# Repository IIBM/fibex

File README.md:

# FIBEX
**FI**UBA **B**rain **EX**plorer

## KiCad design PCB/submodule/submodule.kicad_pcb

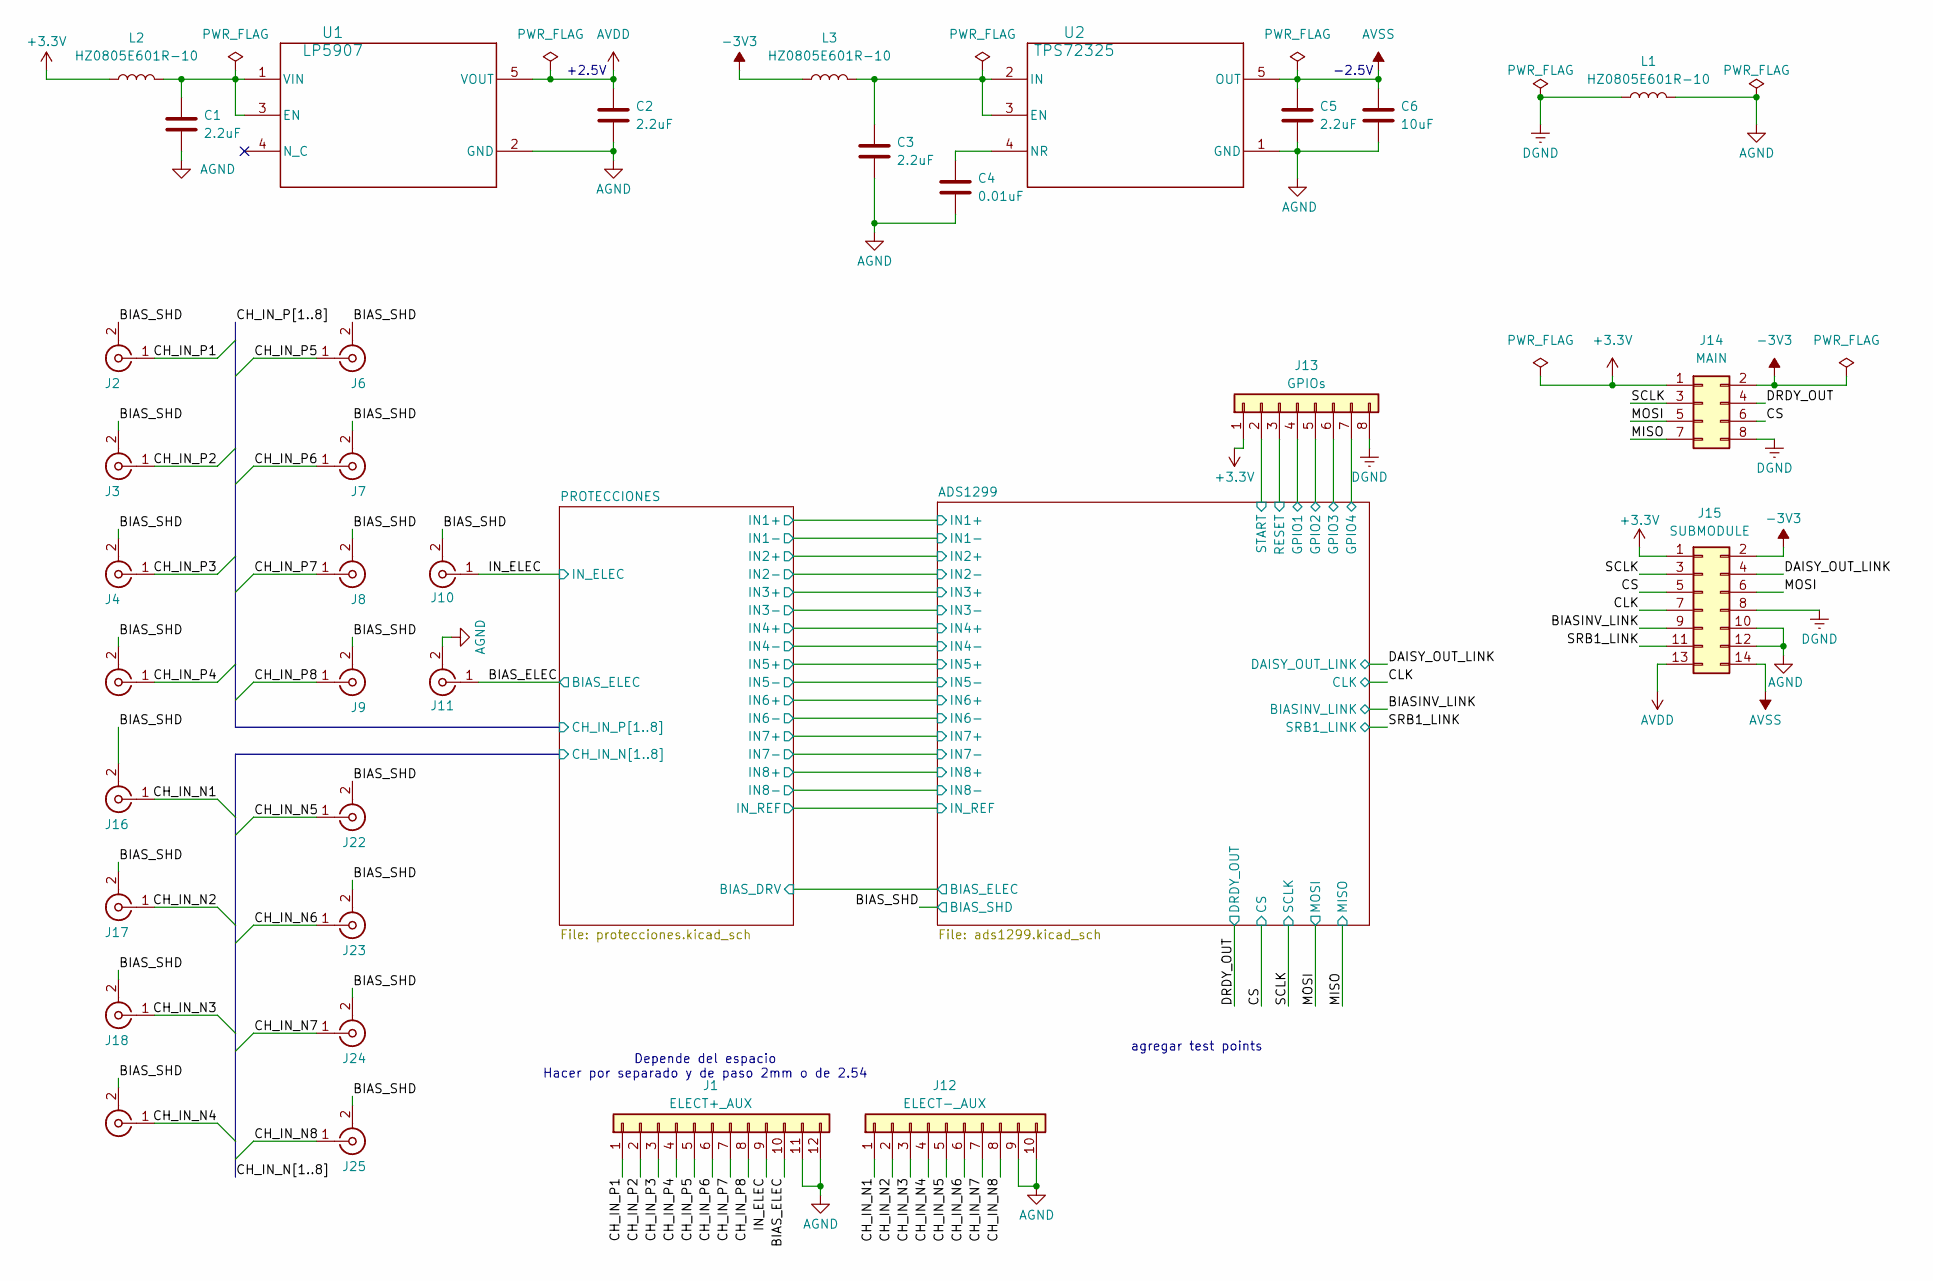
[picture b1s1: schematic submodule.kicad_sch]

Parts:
C1, C2, C3, C5: 2.2uF; C_0603_1608Metric
C4: 0.01uF; C_0603_1608Metric
C6: 10uF; C_0805_2012Metric
J1: ELECT+_AUX; PinHeader_1x12_P1.27mm_Vertical
J2, J3, J4, J5, J6, J7, J8, J9, J10, J11, J16, J17, J18, J21, J22, J23, J24, J25: Conn_Coaxial; U.FL_Molex_MCRF_73412-0110_Vertical
J12: ELECT-_AUX; PinHeader_1x10_P1.27mm_Vertical
J13: GPIOs; PinHeader_1x08_P1.27mm_Vertical
J14: MAIN; IDC-Header_2x04_P2.54mm_Vertical
J15: SUBMODULE; PinHeader_2x07_P1.27mm_Vertical
L1, L2, L3: HZ0805E601R-10; L_0805_2012Metric
U1: LP5907; SOT-23-5_TI_DBV0005A_N
U2: TPS72325; SOT-23-5_TI_DBV0005A_N

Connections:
+3.3V: J13.1, J14.1, J15.1, L2.1; also elsewhere on the board
-3V3: J14.2, J15.2, L3.1
/ADS1299/GPIO1: J13.4; also elsewhere on the board
/ADS1299/GPIO2: J13.5; also elsewhere on the board
/ADS1299/GPIO3: J13.6; also elsewhere on the board
/ADS1299/GPIO4: J13.7; also elsewhere on the board
/ADS1299/RESET: J13.3; also elsewhere on the board
/ADS1299/START: J13.2; also elsewhere on the board
/BIASINV_LINK: J15.9; also elsewhere on the board
/BIAS_ELEC: J1.10, J11.1 (In); also elsewhere on the board
/BIAS_SHD: J2.2 (Ext), J3.2 (Ext), J4.2 (Ext), J5.2 (Ext), J6.2 (Ext), J7.2 (Ext), J8.2 (Ext), J9.2 (Ext), J10.2 (Ext), J16.2 (Ext), J17.2 (Ext), J18.2 (Ext), J21.2 (Ext), J22.2 (Ext), J23.2 (Ext), J24.2 (Ext), J25.2 (Ext); also elsewhere on the board
/CH_IN_N1: J12.1, J16.1 (In); also elsewhere on the board
/CH_IN_N2: J12.2, J17.1 (In); also elsewhere on the board
/CH_IN_N3: J12.3, J18.1 (In); also elsewhere on the board
/CH_IN_N4: J12.4, J21.1 (In); also elsewhere on the board
/CH_IN_N5: J12.5, J22.1 (In); also elsewhere on the board
/CH_IN_N6: J12.6, J23.1 (In); also elsewhere on the board
/CH_IN_N7: J12.7, J24.1 (In); also elsewhere on the board
/CH_IN_N8: J12.8, J25.1 (In); also elsewhere on the board
/CH_IN_P1: J1.1, J2.1 (In); also elsewhere on the board
/CH_IN_P2: J1.2, J3.1 (In); also elsewhere on the board
/CH_IN_P3: J1.3, J4.1 (In); also elsewhere on the board
/CH_IN_P4: J1.4, J5.1 (In); also elsewhere on the board
/CH_IN_P5: J1.5, J6.1 (In); also elsewhere on the board
/CH_IN_P6: J1.6, J7.1 (In); also elsewhere on the board
/CH_IN_P7: J1.7, J8.1 (In); also elsewhere on the board
/CH_IN_P8: J1.8, J9.1 (In); also elsewhere on the board
/CLK: J15.7; also elsewhere on the board
/CS: J14.6, J15.5; also elsewhere on the board
/DAISY_OUT_LINK: J15.4; also elsewhere on the board
/DRDY_OUT: J14.4; also elsewhere on the board
/IN_ELEC: J1.9, J10.1 (In); also elsewhere on the board
/MISO: J14.7; also elsewhere on the board
/MOSI: J14.5, J15.6; also elsewhere on the board
/SCLK: J14.3, J15.3; also elsewhere on the board
/SRB1_LINK: J15.11; also elsewhere on the board
AGND: C1.2, C2.2, C3.2, C4.2, C5.2, C6.2, J1.11, J1.12, J11.2 (Ext), J12.9, J12.10, J15.10, J15.12, L1.2, U1.2 (GND), U2.1 (GND); also elsewhere on the board
AVDD: C2.1, J15.13, U1.5 (VOUT); also elsewhere on the board
AVSS: C5.1, C6.1, J15.14, U2.5 (OUT); also elsewhere on the board
DGND: J13.8, J14.8, J15.8, L1.1; also elsewhere on the board
unnamed: C1.1, L2.2, U1.1 (VIN), U1.3 (EN)
unnamed: C3.1, L3.2, U2.2 (IN), U2.3 (EN)
unnamed: C4.1, U2.4 (NR)

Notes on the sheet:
Depende del espacio Hacer por separado y de paso 2mm o de 2.54
+2.5V
agregar test points
-2.5V

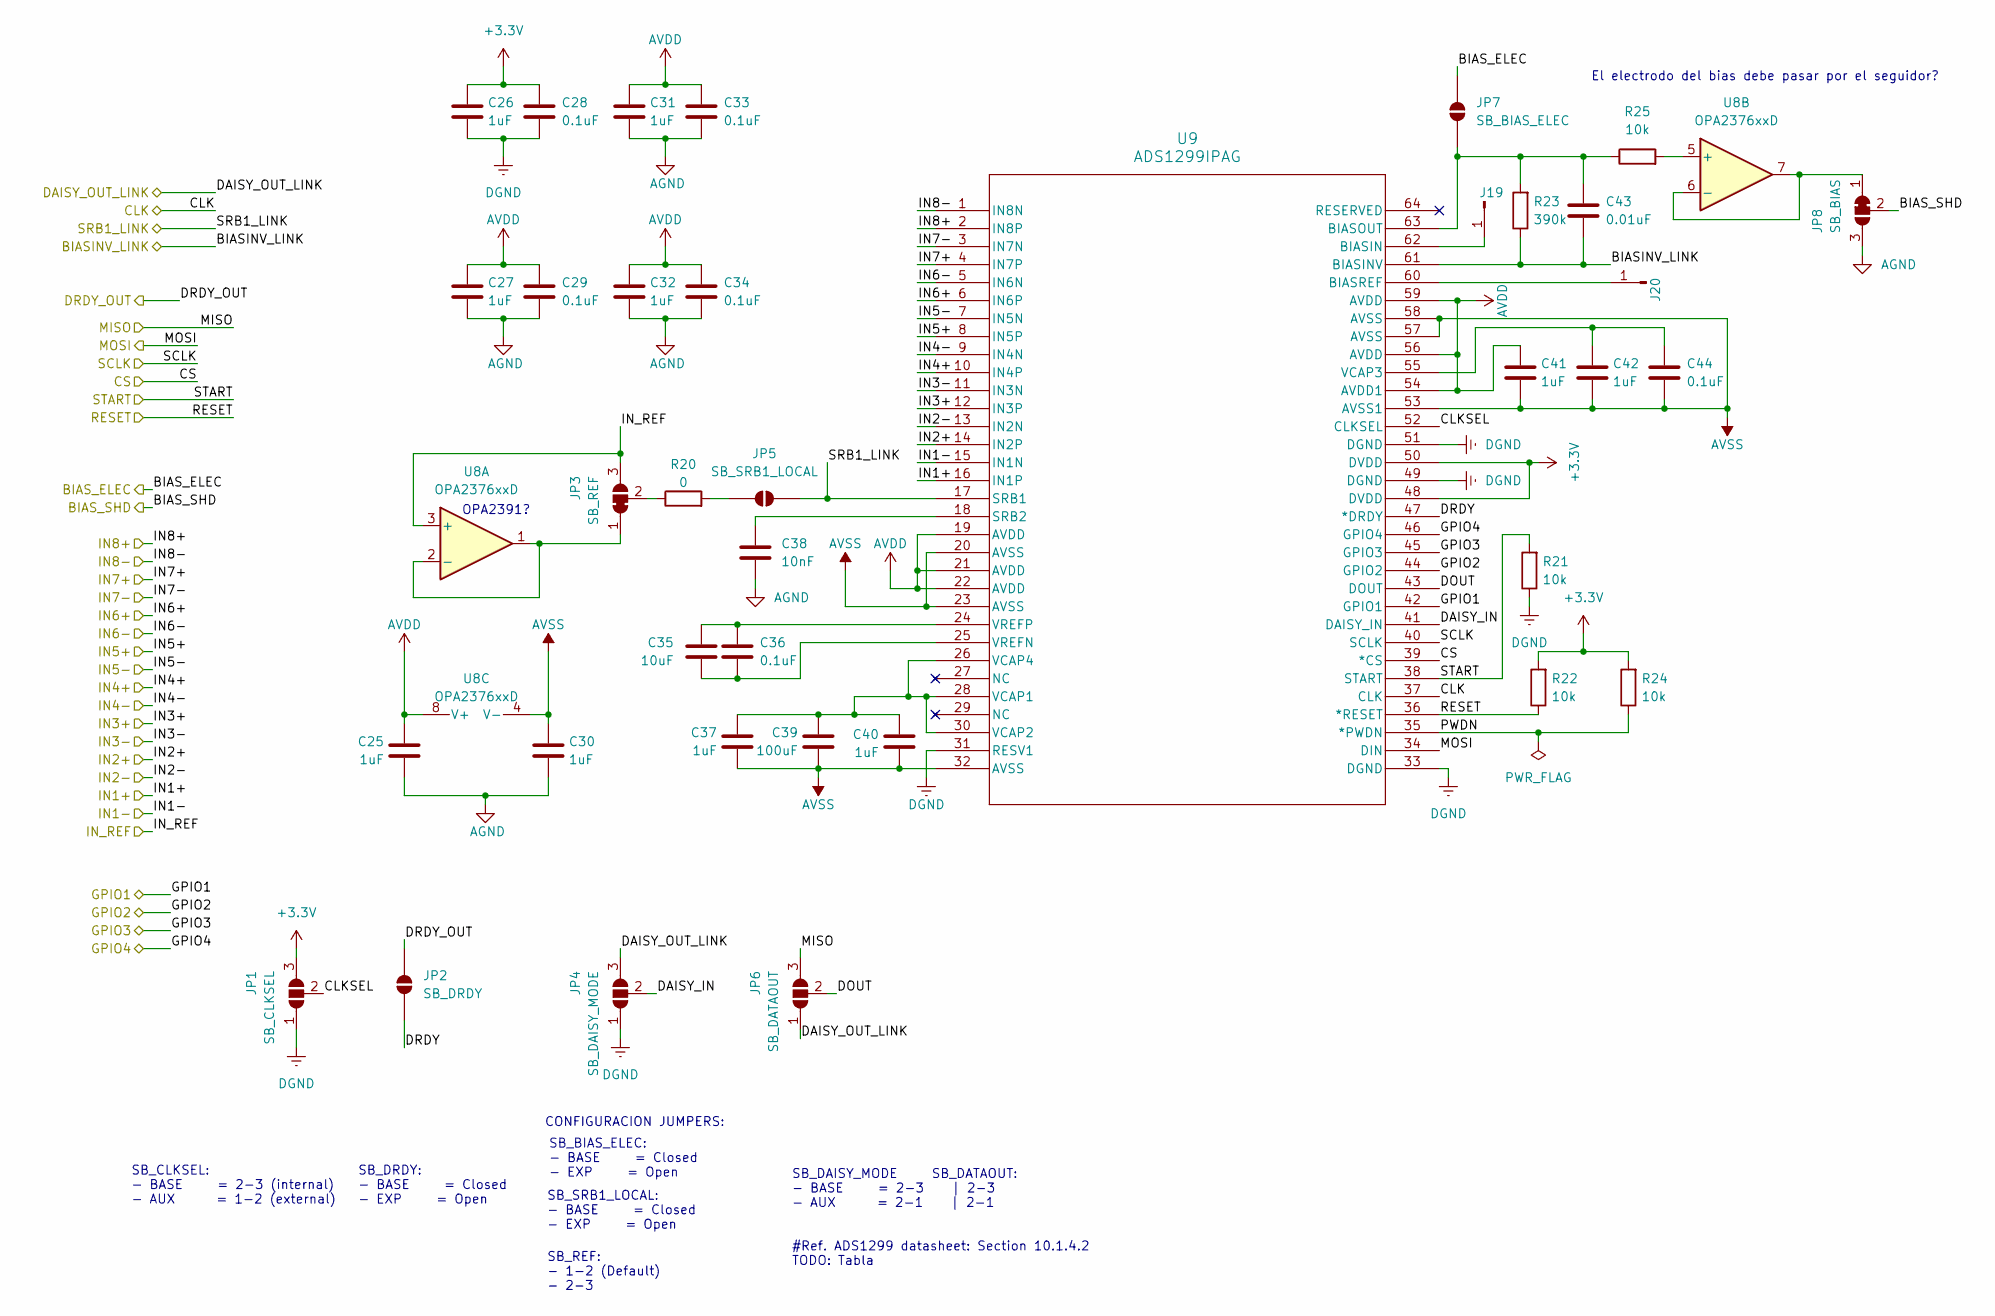
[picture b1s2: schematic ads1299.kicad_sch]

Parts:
C25, C26, C27, C30, C31, C32, C37, C40, C41, C42: 1uF; C_0603_1608Metric
C28, C29, C33, C34, C36, C44: 0.1uF; C_0603_1608Metric
C35: 10uF; C_0805_2012Metric
C38: 10nF; C_0603_1608Metric
C39: 100uF; C_1210_3225Metric
C43: 0.01uF; C_0603_1608Metric
J19, J20: Conn_01x01_Pin; SolderWirePad_1x01_SMD_1x2mm
JP1: SB_CLKSEL; SolderJumper-3_P2.0mm_Open_TrianglePad1.0x1.5mm_NumberLabels
JP2: SB_DRDY; SolderJumper-2_P1.3mm_Open_TrianglePad1.0x1.5mm
JP3: SB_REF; SolderJumper-3_P1.3mm_Bridged12_Pad1.0x1.5mm_NumberLabels
JP4: SB_DAISY_MODE; SolderJumper-3_P2.0mm_Open_TrianglePad1.0x1.5mm_NumberLabels
JP5: SB_SRB1_LOCAL; SolderJumper-2_P1.3mm_Open_TrianglePad1.0x1.5mm
JP6: SB_DATAOUT; SolderJumper-3_P2.0mm_Open_TrianglePad1.0x1.5mm_NumberLabels
JP7: SB_BIAS_ELEC; SolderJumper-2_P1.3mm_Open_TrianglePad1.0x1.5mm
JP8: SB_BIAS; SolderJumper-3_P1.3mm_Bridged12_Pad1.0x1.5mm_NumberLabels
R20: 0; R_0603_1608Metric
R21, R22, R24, R25: 10k; R_0603_1608Metric
R23: 390k; R_0603_1608Metric
U8: OPA2376xxD; SOIC-8_5.3x6.2mm_P1.27mm
U9: ADS1299IPAG; PAG64_TEX

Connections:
+3.3V: C26.1, C28.1, JP1.3 (B), R22.2, R24.2, U9.48 (DVDD), U9.50 (DVDD); also elsewhere on the board
/ADS1299/BIAS_ELEC: JP7.2 (B); also elsewhere on the board
/ADS1299/CLKSEL: JP1.2 (C), U9.52 (CLKSEL)
/ADS1299/DAISY_IN: JP4.2 (C), U9.41 (DAISY_IN)
/ADS1299/DOUT: JP6.2 (C), U9.43 (DOUT)
/ADS1299/DRDY: JP2.2 (B), U9.47 (*DRDY)
/ADS1299/GPIO1: U9.42 (GPIO1); also elsewhere on the board
/ADS1299/GPIO2: U9.44 (GPIO2); also elsewhere on the board
/ADS1299/GPIO3: U9.45 (GPIO3); also elsewhere on the board
/ADS1299/GPIO4: U9.46 (GPIO4); also elsewhere on the board
/ADS1299/IN1+: U9.16 (IN1P); also elsewhere on the board
/ADS1299/IN1-: U9.15 (IN1N); also elsewhere on the board
/ADS1299/IN2+: U9.14 (IN2P); also elsewhere on the board
/ADS1299/IN2-: U9.13 (IN2N); also elsewhere on the board
/ADS1299/IN3+: U9.12 (IN3P); also elsewhere on the board
/ADS1299/IN3-: U9.11 (IN3N); also elsewhere on the board
/ADS1299/IN4+: U9.10 (IN4P); also elsewhere on the board
/ADS1299/IN4-: U9.9 (IN4N); also elsewhere on the board
/ADS1299/IN5+: U9.8 (IN5P); also elsewhere on the board
/ADS1299/IN5-: U9.7 (IN5N); also elsewhere on the board
/ADS1299/IN6+: U9.6 (IN6P); also elsewhere on the board
/ADS1299/IN6-: U9.5 (IN6N); also elsewhere on the board
/ADS1299/IN7+: U9.4 (IN7P); also elsewhere on the board
/ADS1299/IN7-: U9.3 (IN7N); also elsewhere on the board
/ADS1299/IN8+: U9.2 (IN8P); also elsewhere on the board
/ADS1299/IN8-: U9.1 (IN8N); also elsewhere on the board
/ADS1299/IN_REF: JP3.3 (B), U8.3 (+); also elsewhere on the board
/ADS1299/PWDN: R24.1, U9.35 (*PWDN)
/ADS1299/RESET: R22.1, U9.36 (*RESET); also elsewhere on the board
/ADS1299/START: R21.2, U9.38 (START); also elsewhere on the board
/BIASINV_LINK: C43.2, R23.1, U9.61 (BIASINV); also elsewhere on the board
/BIAS_SHD: JP8.2 (C); also elsewhere on the board
/CLK: U9.37 (CLK); also elsewhere on the board
/CS: U9.39 (*CS); also elsewhere on the board
/DAISY_OUT_LINK: JP4.3 (B), JP6.1 (A); also elsewhere on the board
/DRDY_OUT: JP2.1 (A); also elsewhere on the board
/MISO: JP6.3 (B); also elsewhere on the board
/MOSI: U9.34 (DIN); also elsewhere on the board
/SCLK: U9.40 (SCLK); also elsewhere on the board
/SRB1_LINK: JP5.1 (A), U9.17 (SRB1); also elsewhere on the board
AGND: C25.2, C27.2, C29.2, C30.2, C31.2, C32.2, C33.2, C34.2, C38.2, JP8.3 (B); also elsewhere on the board
AVDD: C25.1, C27.1, C29.1, C31.1, C32.1, C33.1, C34.1, C41.1, U8.8 (V+), U9.19 (AVDD), U9.21 (AVDD), U9.22 (AVDD), U9.54 (AVDD1), U9.56 (AVDD), U9.59 (AVDD); also elsewhere on the board
AVSS: C30.1, C37.2, C39.2, C40.2, C41.2, C42.2, C44.2, U8.4 (V-), U9.20 (AVSS), U9.23 (AVSS), U9.32 (AVSS), U9.53 (AVSS1), U9.57 (AVSS), U9.58 (AVSS); also elsewhere on the board
DGND: C26.2, C28.2, JP1.1 (A), JP4.1 (A), R21.1, U9.31 (RESV1), U9.33 (DGND), U9.49 (DGND), U9.51 (DGND); also elsewhere on the board
unnamed: J19.1 (Pin_1_1), U9.62 (BIASIN)
unnamed: J20.1 (Pin_1_1), U9.60 (BIASREF)
unnamed: JP3.1 (A), U8.1, U8.2 (-)
unnamed: JP3.2 (C), R20.1
unnamed: JP5.2 (B), R20.2
unnamed: C43.1, JP7.1 (A), R23.2, R25.1, U9.63 (BIASOUT)
unnamed: JP8.1 (A), U8.6 (-), U8.7
unnamed: R25.2, U8.5 (+)
unnamed: C38.1, U9.18 (SRB2)
unnamed: C37.1, C39.1, C40.1, U9.26 (VCAP4), U9.28 (VCAP1), U9.30 (VCAP2)
unnamed: C42.1, C44.1, U9.55 (VCAP3)
unnamed: C35.2, C36.2, U9.25 (VREFN)
unnamed: C35.1, C36.1, U9.24 (VREFP)

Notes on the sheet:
SB_REF: - 1-2 (Default) - 2-3
OPA2391?
El electrodo del bias debe pasar por el seguidor?
SB_DAISY_MODE SB_DATAOUT: - BASE = 2-3 | 2-3 - AUX = 2-1 | 2-1 #Ref. ADS1299 datasheet: Section 10.1.4.2 TODO: Tabla
SB_SRB1_LOCAL: - BASE = Closed - EXP = Open
SB_BIAS_ELEC: - BASE = Closed - EXP = Open
SB_CLKSEL: - BASE = 2-3 (internal) - AUX = 1-2 (external)
SB_DRDY: - BASE = Closed - EXP = Open
CONFIGURACION JUMPERS:

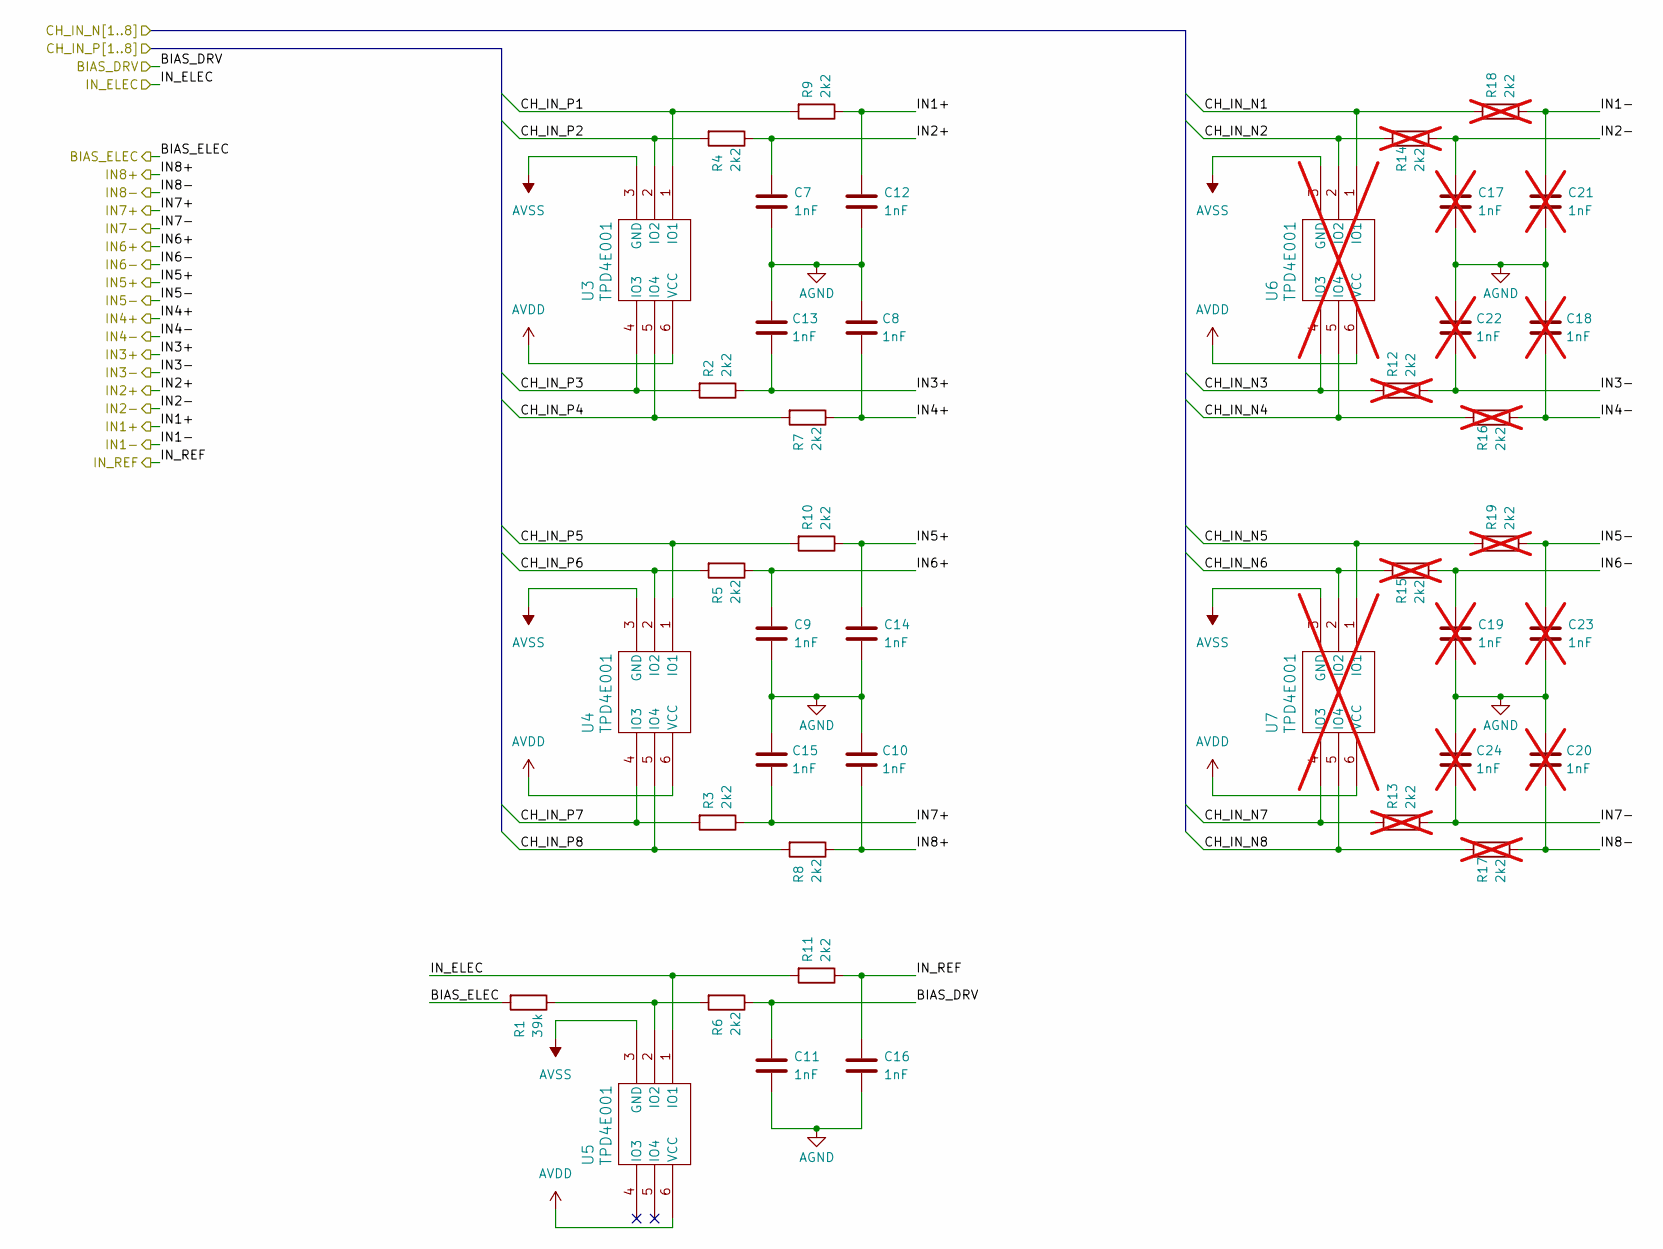
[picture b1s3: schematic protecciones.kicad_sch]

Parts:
C7, C8, C9, C10, C11, C12, C13, C14, C15, C16: 1nF; C_0603_1608Metric
C17, C18, C19, C20, C21, C22, C23, C24: 1nF; C_0603_1608Metric; not fitted
R1: 39k; R_0603_1608Metric
R2, R3, R4, R5, R6, R7, R8, R9, R10, R11: 2k2; R_0603_1608Metric
R12, R13, R14, R15, R16, R17, R18, R19: 2k2; R_0603_1608Metric; not fitted
U3, U4, U5: TPD4E001; DPK6
U6, U7: TPD4E001; DPK6; not fitted

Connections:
/ADS1299/BIAS_ELEC: C11.1, R6.1; also elsewhere on the board
/ADS1299/IN1+: C12.1, R9.1; also elsewhere on the board
/ADS1299/IN1-: C21.1, R18.1; also elsewhere on the board
/ADS1299/IN2+: C7.1, R4.1; also elsewhere on the board
/ADS1299/IN2-: C17.1, R14.1; also elsewhere on the board
/ADS1299/IN3+: C8.1, R2.1; also elsewhere on the board
/ADS1299/IN3-: C18.1, R12.1; also elsewhere on the board
/ADS1299/IN4+: C13.1, R7.1; also elsewhere on the board
/ADS1299/IN4-: C22.1, R16.1; also elsewhere on the board
/ADS1299/IN5+: C14.1, R10.1; also elsewhere on the board
/ADS1299/IN5-: C23.1, R19.1; also elsewhere on the board
/ADS1299/IN6+: C9.1, R5.1; also elsewhere on the board
/ADS1299/IN6-: C19.1, R15.1; also elsewhere on the board
/ADS1299/IN7+: C10.1, R3.1; also elsewhere on the board
/ADS1299/IN7-: C20.1, R13.1; also elsewhere on the board
/ADS1299/IN8+: C15.1, R8.1; also elsewhere on the board
/ADS1299/IN8-: C24.1, R17.1; also elsewhere on the board
/ADS1299/IN_REF: C16.1, R11.1; also elsewhere on the board
/BIAS_ELEC: R1.2; also elsewhere on the board
/CH_IN_N1: R18.2, U6.1 (IO1); also elsewhere on the board
/CH_IN_N2: R14.2, U6.2 (IO2); also elsewhere on the board
/CH_IN_N3: R12.2, U6.4 (IO3); also elsewhere on the board
/CH_IN_N4: R16.2, U6.5 (IO4); also elsewhere on the board
/CH_IN_N5: R19.2, U7.1 (IO1); also elsewhere on the board
/CH_IN_N6: R15.2, U7.2 (IO2); also elsewhere on the board
/CH_IN_N7: R13.2, U7.4 (IO3); also elsewhere on the board
/CH_IN_N8: R17.2, U7.5 (IO4); also elsewhere on the board
/CH_IN_P1: R9.2, U3.1 (IO1); also elsewhere on the board
/CH_IN_P2: R4.2, U3.2 (IO2); also elsewhere on the board
/CH_IN_P3: R2.2, U3.4 (IO3); also elsewhere on the board
/CH_IN_P4: R7.2, U3.5 (IO4); also elsewhere on the board
/CH_IN_P5: R10.2, U4.1 (IO1); also elsewhere on the board
/CH_IN_P6: R5.2, U4.2 (IO2); also elsewhere on the board
/CH_IN_P7: R3.2, U4.4 (IO3); also elsewhere on the board
/CH_IN_P8: R8.2, U4.5 (IO4); also elsewhere on the board
/IN_ELEC: R11.2, U5.1 (IO1); also elsewhere on the board
AGND: C7.2, C8.2, C9.2, C10.2, C11.2, C12.2, C13.2, C14.2, C15.2, C16.2, C17.2, C18.2, C19.2, C20.2, C21.2, C22.2, C23.2, C24.2; also elsewhere on the board
AVDD: U3.6 (VCC), U4.6 (VCC), U5.6 (VCC), U6.6 (VCC), U7.6 (VCC); also elsewhere on the board
AVSS: U3.3 (GND), U4.3 (GND), U5.3 (GND), U6.3 (GND), U7.3 (GND); also elsewhere on the board
unnamed: R1.1, R6.2, U5.2 (IO2)

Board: 4 copper layers, 116 parts (0 on the bottom side), 80 nets, no tracks yet.

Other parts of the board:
J16#2, J17#2: Conn_01x01_Pin; PinHeader_1x01_P2.54mm_Vertical
